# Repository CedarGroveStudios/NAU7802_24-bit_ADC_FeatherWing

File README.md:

# NAU7802_24-bit_ADC_FeatherWing

### Custom 24-bit load cell sensor ADC with dual analog inputs powered by CircuitPython.

[NAU7802 CircuitPython Driver: Class Description](https://github.com/CedarGroveStudios/NAU7802_24-bit_ADC_FeatherWing/blob/main/docs/pseudo%20readthedocs%20cedargrove_nau7802.pdf)

NAU7802 FeatherWing 16-SOIC (SMD) Version:

<a href="https://oshpark.com/shared_projects/qFvEU3Bn"></img></a>

NAU7802 FeatherWing  16-DIP (THT) Version:

<a href="https://oshpark.com/shared_projects/ZfryHYnc"></img></a>

Needing a calibration weight? The U.S. Mint coin specifications might have some information that could help -- if you have some spare change. https://www.usmint.gov/learn/coin-and-medal-programs/coin-specifications

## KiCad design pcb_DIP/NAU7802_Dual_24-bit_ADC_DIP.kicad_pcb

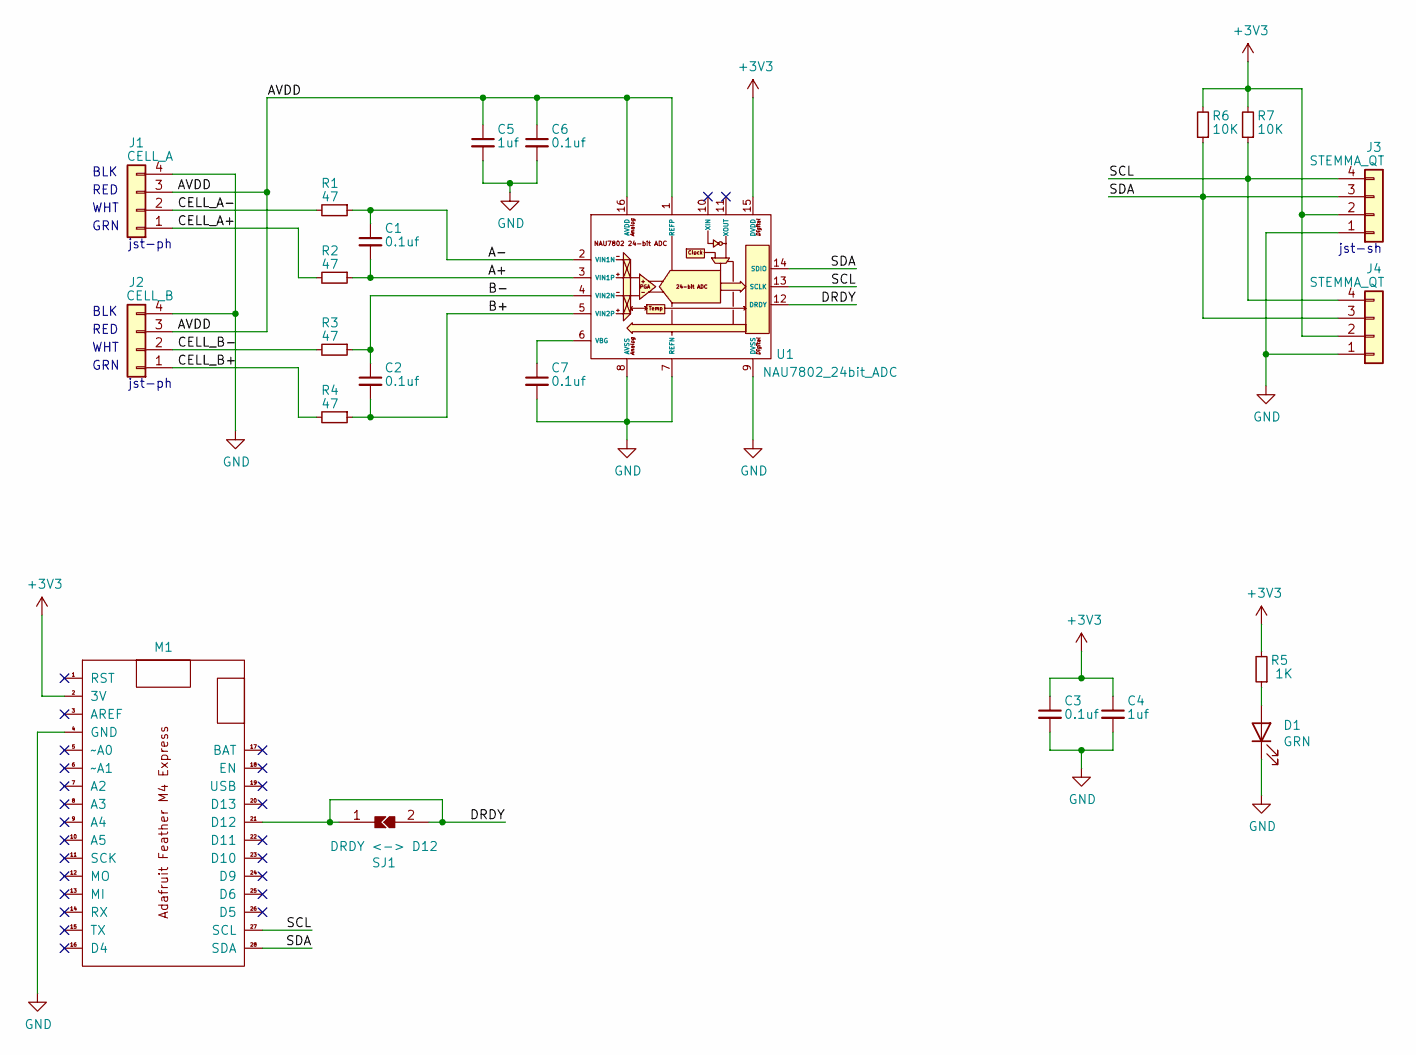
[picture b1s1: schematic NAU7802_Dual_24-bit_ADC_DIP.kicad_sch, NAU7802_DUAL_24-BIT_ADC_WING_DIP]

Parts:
C1, C2, C3, C6, C7: 0.1uf; C_0805_2012Metric
C4, C5: 1uf; C_0805_2012Metric
D1: GRN; LED_0805_2012Metric
J1: CELL_A; JST_PH_S4B-PH-SM4-TB_1x04-1MP_P2.00mm_Horizontal
J2: CELL_B; JST_PH_S4B-PH-SM4-TB_1x04-1MP_P2.00mm_Horizontal
J3, J4: STEMMA_QT; JST_SH_SM04B-SRSS-TB_1x04-1MP_P1.00mm_Horizontal
M1: Feather_M4_Express; Adafruit Feather
R1, R2, R3, R4: 47; R_0805_2012Metric
R5: 1K; R_0805_2012Metric
R6, R7: 10K; R_0805_2012Metric
SJ1: DRDY <-> D12; 0805_Solder_Jumper
U1: NAU7802_24bit_ADC; DIP-16_W7.62mm_Socket

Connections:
+3V3: C3.1, C4.1, J3.2, J4.2, M1.2 (3V), R5.2, R6.2, R7.2, U1.15 (DVDD)
/A+: C1.2, R2.1, U1.3 (VIN1P)
/A-: C1.1, R1.1, U1.2 (VIN1N)
/AVDD: C5.1, C6.1, J1.3, J2.3, U1.1 (REFP), U1.16 (AVDD)
/B+: C2.2, R4.1, U1.5 (VIN2P)
/B-: C2.1, R3.1, U1.4 (VIN2N)
/CELL_A+: J1.1, R2.2
/CELL_A-: J1.2, R1.2
/CELL_B+: J2.1, R4.2
/CELL_B-: J2.2, R3.2
/DRDY: M1.21 (D12), SJ1.1, SJ1.2, U1.12 (DRDY)
/SCL: J3.4, J4.4, M1.27 (SCL), R7.1, U1.13 (SCLK)
/SDA: J3.3, J4.3, M1.28 (SDA), R6.1, U1.14 (SDIO)
GND: C3.2, C4.2, C5.2, C6.2, C7.2, D1.1 (K), J1.4, J2.4, J3.1, J4.1, M1.4 (GND), U1.7 (REFN), U1.8 (AVSS), U1.9 (DVSS)
unnamed: C7.1, U1.6 (VBG)
unnamed: D1.2 (A), R5.1

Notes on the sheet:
RED
GRN
jst-sh
BLK
WHT
jst-ph

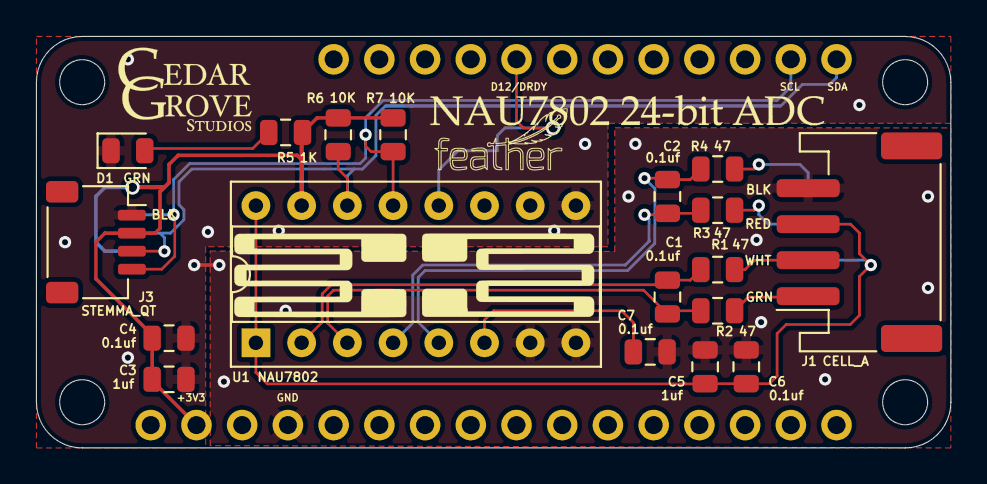
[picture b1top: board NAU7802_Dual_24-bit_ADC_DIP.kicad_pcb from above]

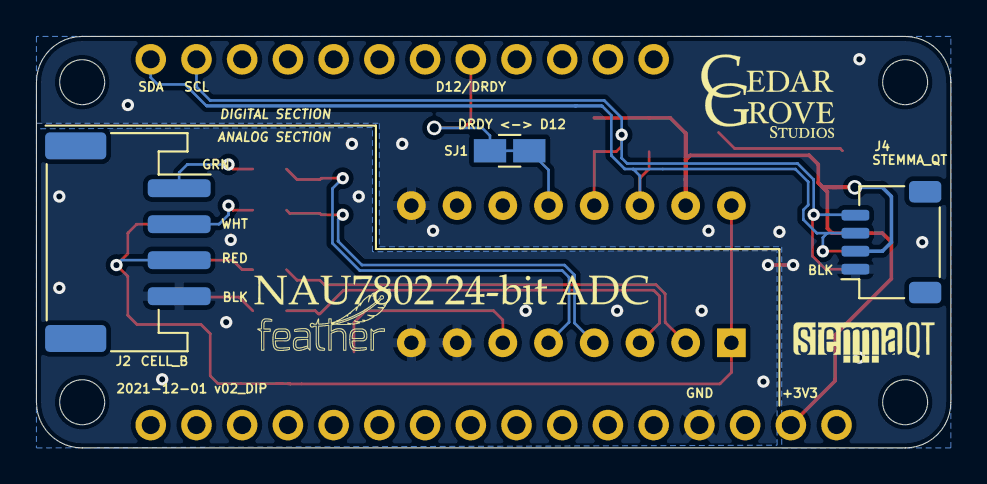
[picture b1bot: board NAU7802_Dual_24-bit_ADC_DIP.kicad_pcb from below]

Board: 2 copper layers, 50.8 x 22.9 mm, 23 parts (3 on the bottom side), 16 nets.

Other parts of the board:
REF: MountingHole_2.5mm

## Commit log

2020-11-24 initial repo load
2020-11-26 add clue_scale example
2020-11-27 update for 2-channel operation
2020-11-28 update PCB silk design
2020-11-29 update PCB design
2020-11-29 update clue_scale_code.py example
2020-11-29 update documentation
2020-12-23 update annotated graphics
2020-12-24 update documentation; add calib example
2020-12-30 add calibrate method
2021-01-02 add .mpy version
2021-01-07 update calibration method
2021-01-07 update clue_scale example
2021-01-08 Update LICENSE
2021-01-09 update single channel example; begin work on dual channel version
2021-01-10 update driver for channel switch settling time; continue work on examples
2021-01-10 update driver with channel select settling delay; continue work on examples
2021-01-11 update driver and examples
2021-01-11 cleanup working files
2021-01-11 update clue scale image folder
2021-01-17 update example
2021-02-19 update with OSHPark link
2021-12-02 refactor SMD wing to accept ADC DIP pkg
2021-12-02 refactor wing for NAU7802 ADC DIP package
2021-12-07 add DIP package version
2022-01-12 update to newest kicad version
2022-01-31 add photo of refactored 16-DIP version
2022-03-11 add oshpark and sparkfun links
2022-04-20 update version information and documentation
2022-04-20 update with PCB copper images
2022-04-20 improve calibration performance
2022-04-23 eliminate dependency on micropython.const
2022-04-24 update to match community bundle repo
2022-04-24 update NAU7802 driver class
2022-04-26 update gitignore
2023-02-01 Remove
